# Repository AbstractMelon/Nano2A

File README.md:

# Nano2A

An open-source micro AFHDS2A (FlySky) receiver.

## Features

- **Protocol:** AFHDS2A (FlySky)
- **Outputs:** PWM (3ch)
- **Input voltage:** 6.4–22.2V (2S–6S LiPo)
- **Weight:** < 3g
- **Size:** 13.75×15mm PCB
- **Range:** 300m+ (open field)
- **Telemetry:** Battery voltage sensing (ADC)
- **Cost:** ~$1.81 BOM + ~$0.4 PCB (~$2.20/unit)

## Build It

| Item | Source | Cost |
|---|---|---|
| PCBs | JLCPCB (see /PCB) | $0.39 |
| Parts | LCSC / AliExpress | $1.81 |
| **Total per unit** | | **$2.21** |

See [PARTS.md](PARTS.md) for the detailed BOM.

### Programming

2-pin SWD header (SWDIO, SWCLK).

Firmware build: (coming soon)

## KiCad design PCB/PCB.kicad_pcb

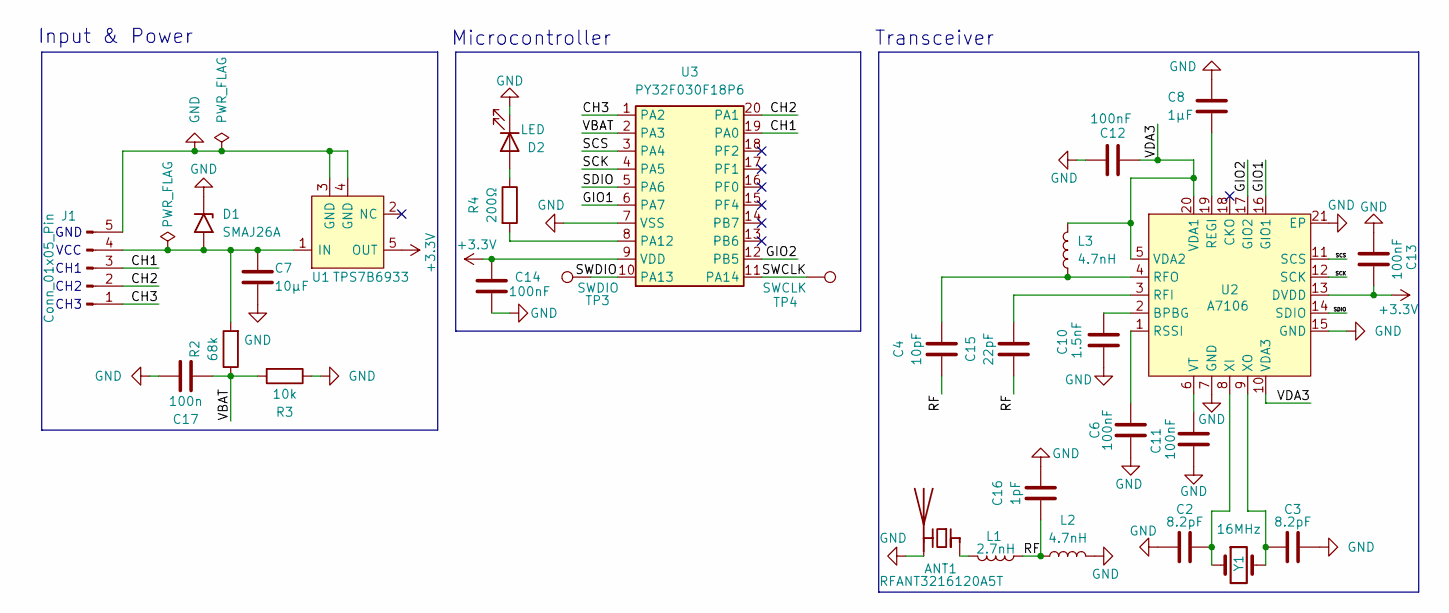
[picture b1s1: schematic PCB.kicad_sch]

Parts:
ANT1: RFANT3216120A5T; L_1206_3216Metric; LCSC C127629
C2, C3: 8.2pF; C_0402_1005Metric; LCSC C1555
C4: 10pF; C_0402_1005Metric; LCSC C1555
C6, C11, C12, C13, C14: 100nF; C_0402_1005Metric; LCSC C41851
C7: 10µF; C_0603_1608Metric; LCSC C19702
C8: 1µF; C_0402_1005Metric
C10: 1.5nF; C_0402_1005Metric; LCSC C41851
C15: 22pF; C_0402_1005Metric; LCSC C1555
C16: 1pF; C_0402_1005Metric; LCSC C1555
C17: 100n; C_0402_1005Metric; LCSC C1555
D1: SMAJ26A; D_SMA
D2: LED; LED_0603_1608Metric
J1: Conn_01x05_Pin; PinHeader_1x05_P2.54mm_Horizontal
L1: 2.7nH; L_0402_1005Metric; LCSC C91240
L2, L3: 4.7nH; L_0402_1005Metric
R2: 68k; R_0402_1005Metric
R3: 10k; R_0402_1005Metric
R4: 200Ω; R_0402_1005Metric
TP3: SWDIO; TestPoint_Pad_D1.0mm
TP4: SWCLK; TestPoint_Pad_D1.0mm
U1: TPS7B6933; SOT-23-5
U2: A7106; QFN-20-1EP_4x4mm_P0.5mm_EP2.5x2.5mm
U3: PY32F030F18P6; TSSOP-20_4.4x6.5mm_P0.65mm
Y1: 16MHz; Crystal_SMD_3225-4Pin_3.2x2.5mm; LCSC C13738

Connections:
+3.3V: C13.1, C14.1, U1.5 (OUT), U2.13 (DVDD), U3.9 (VDD)
/CH1: J1.3, U3.19 (PA0)
/CH2: J1.2, U3.20 (PA1)
/CH3: J1.1, U3.1 (PA2)
/GIO1: U2.16 (GIO1), U3.6 (PA7)
/GIO2: U2.17 (GIO2), U3.12 (PB5)
/RF: C4.1, C15.1, C16.1, L1.1, L2.1
/SCK: U2.12 (SCK), U3.4 (PA5)
/SCS: U2.11 (SCS), U3.3 (PA4)
/SDIO: U2.14 (SDIO), U3.5 (PA6)
/SWCLK: TP4.1 (1_1), U3.11 (PA14)
/SWDIO: TP3.1 (1_1), U3.10 (PA13)
/VBAT: C17.1, R2.1, R3.2, U3.2 (PA3)
/VDA3: C12.2, L3.2, U2.5 (VDA2), U2.10 (VDA3), U2.20 (VDA1)
GND: ANT1.2 (PCB_Trace), C2.1, C3.2, C6.1, C7.1, C8.1, C10.2, C11.2, C12.1, C13.2, C14.2, C16.2, C17.2, D1.1 (A1), D2.1 (K), J1.5, L2.2, R3.1, U1.3 (GND), U1.4 (GND), U2.7 (GND), U2.15 (GND), U2.21 (EP), U3.7 (VSS)
unnamed: ANT1.1 (FEED), L1.2
unnamed: C7.2, D1.2 (A2), J1.4, R2.2, U1.1 (IN)
unnamed: D2.2 (A), R4.1
unnamed: C10.1, U2.2 (BPBG)
unnamed: C8.2, U2.19 (REGI)
unnamed: C15.2, U2.3 (RFI)
unnamed: C4.2, L3.1, U2.4 (RFO)
unnamed: C6.2, U2.1 (RSSI)
unnamed: C11.1, U2.6 (VT)
unnamed: C2.2, U2.8 (XI), Y1.1
unnamed: C3.1, U2.9 (XO), Y1.2
unnamed: R4.2, U3.8 (PA12)

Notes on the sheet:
GND
Input & Power
CH2
CH1
CH3
Transceiver
Microcontroller
VCC

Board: 2 copper layers, 30 parts (0 on the bottom side), 27 nets, no tracks yet.

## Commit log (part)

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2026-06-10 feat: add kicad project
2026-06-10 feat: add kicad configuration
2026-06-10 feat: add kicad gitignore
2026-06-10 feat: add readme
2026-06-10 feat: Update PCB with size and pads
2026-06-10 feat: update README.md
2026-06-10 feat: add components
2026-06-10 fix: correct readme wording
2026-06-10 feat: added all components
2026-06-10 feat: rename channels and organise
2026-06-14 feat: update PCB traces and move components
2026-06-14 feat: Add .gitignore
2026-06-15 fix: update gitignore
2026-06-15 fix: update reaadme to match board
2026-06-15 feat: Add parts list
2026-06-15 fix: add component values
2026-06-15 feat: add LTSC part numbers
2026-06-15 fix: update PCB size and U2 package
2026-06-15 feat: Add symbol libraries for A7106
2026-06-15 feat: Update schematic
2026-06-15 feat: update PCB from schematic
2026-06-15 fix: Migrate symbol
2026-06-15 feat: Update PCB
2026-06-15 PCB changes
2026-06-15 fix: position component
2026-06-26 fix: Update readme pricing
2026-06-26 fix: Update packagge for A7106
2026-06-26 Update PCB
2026-06-26 fix: Update BOM
2026-06-26 feat: Update Schematic lables
2026-06-26 Blank PCB state
2026-06-27 fix: Update readme specs
